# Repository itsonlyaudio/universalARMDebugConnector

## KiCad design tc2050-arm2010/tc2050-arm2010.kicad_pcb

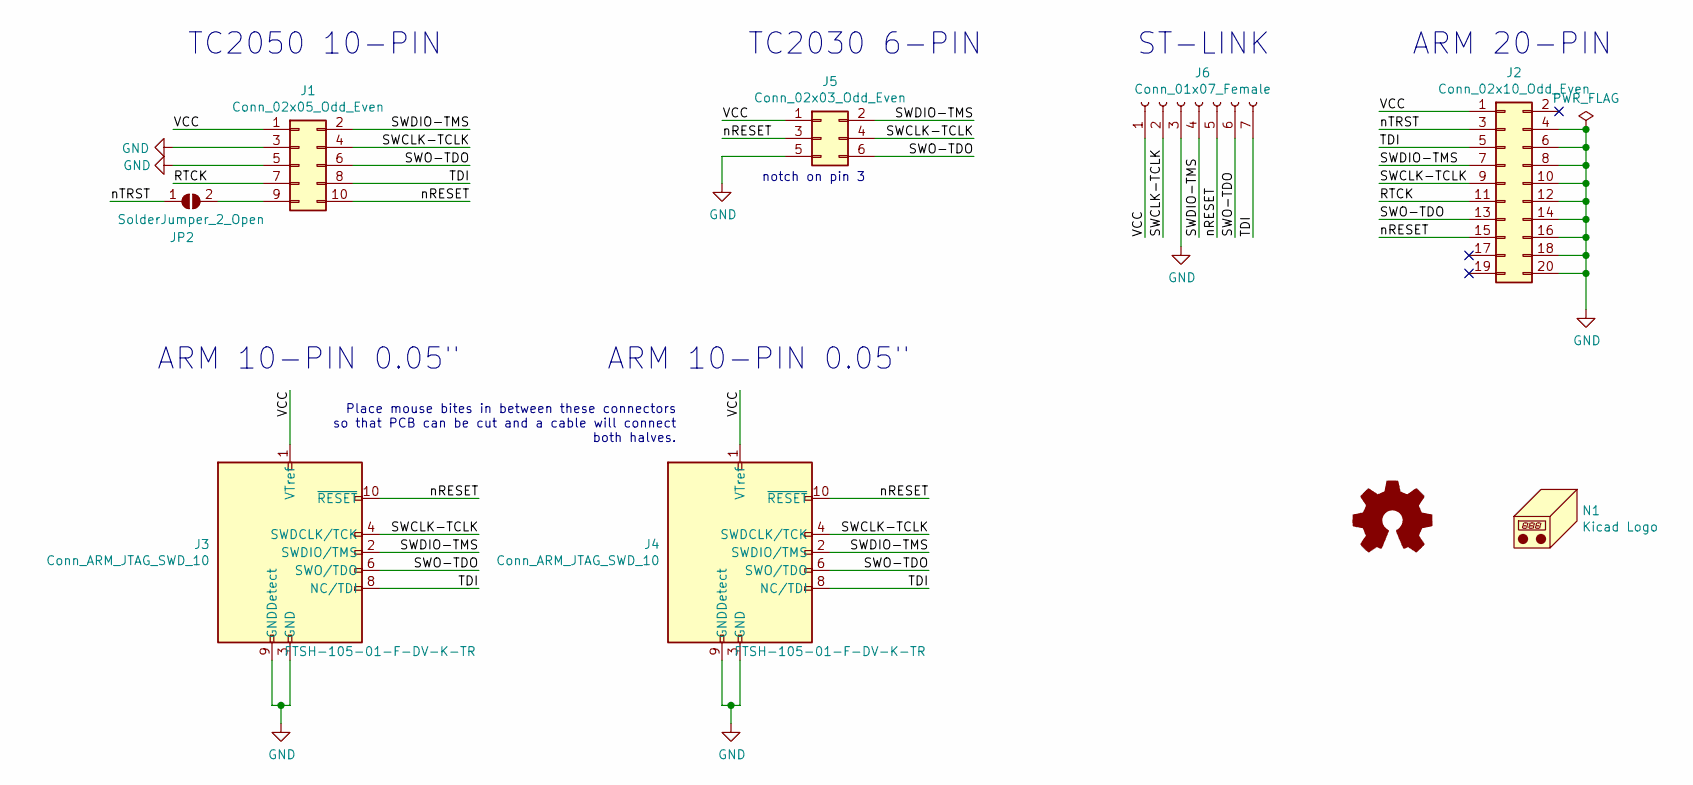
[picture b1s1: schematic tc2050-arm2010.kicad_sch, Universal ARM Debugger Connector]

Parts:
J1: Conn_02x05_Odd_Even; IDC-Header_2x05_P2.54mm_Vertical
J2: Conn_02x10_Odd_Even; PinSocket_2x10_P2.54mm_Horizontal
J3: Conn_ARM_JTAG_SWD_10; Samtec_MECF-05-02-NP-L-DV_2x05_P1.27mm_Socket_Horizontal; Partno FTSH-105-01-F-DV-K-TR; Digikey SAM13160CT-ND
J4: Conn_ARM_JTAG_SWD_10; Samtec_MECF-05-02-NP-L-DV_2x05_P1.27mm_Socket_Horizontal; Partno FTSH-105-01-F-DV-K-TR; Digikey SAM89SAM13160CT-ND
J5: Conn_02x03_Odd_Even; IDC-Header_2x03_P2.54mm_Vertical
J6: Conn_01x07_Female; PinHeader_1x07_P2.54mm_Vertical
JP2: SolderJumper_2_Open; SolderJumper-2_P1.3mm_Open_RoundedPad1.0x1.5mm
LOGO1: Logo_Open_Hardware_Small; OSHW-Logo2_7.3x6mm_SilkScreen
N1: Kicad Logo; KiCad-Logo2_5mm_SilkScreen

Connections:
/RTCK: J1.7, J2.11
/SWCLK-TCLK: J1.4, J2.9, J3.4 (SWDCLK/TCK), J4.4 (SWDCLK/TCK), J5.4, J6.2
/SWDIO-TMS: J1.2, J2.7, J3.2 (SWDIO/TMS), J4.2 (SWDIO/TMS), J5.2, J6.4
/SWO-TDO: J1.6, J2.13, J3.6 (SWO/TDO), J4.6 (SWO/TDO), J5.6, J6.6
/TDI: J1.8, J2.5, J3.8 (NC/TDI), J4.8 (NC/TDI), J6.7
/VCC: J1.1, J2.1, J3.1 (VTref), J4.1 (VTref), J5.1, J6.1
/nRESET: J1.10, J2.15, J3.10 (~RESET~), J4.10 (~RESET~), J5.3, J6.5
/nTRST: J2.3, JP2.1 (A)
GND: J1.3, J1.5, J2.4, J2.6, J2.8, J2.10, J2.12, J2.14, J2.16, J2.18, J2.20, J3.3 (GND), J3.5 (GND), J3.9 (GNDDetect), J4.3 (GND), J4.5 (GND), J4.9 (GNDDetect), J5.5, J6.3
unnamed: J1.9, JP2.2 (B)

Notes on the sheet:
TC2050 10-PIN
ARM 10-PIN 0.05"
Place mouse bites in between these connectors so that PCB can be cut and a cable will connect both halves.
notch on pin 3
TC2030 6-PIN
ST-LINK
ARM 20-PIN

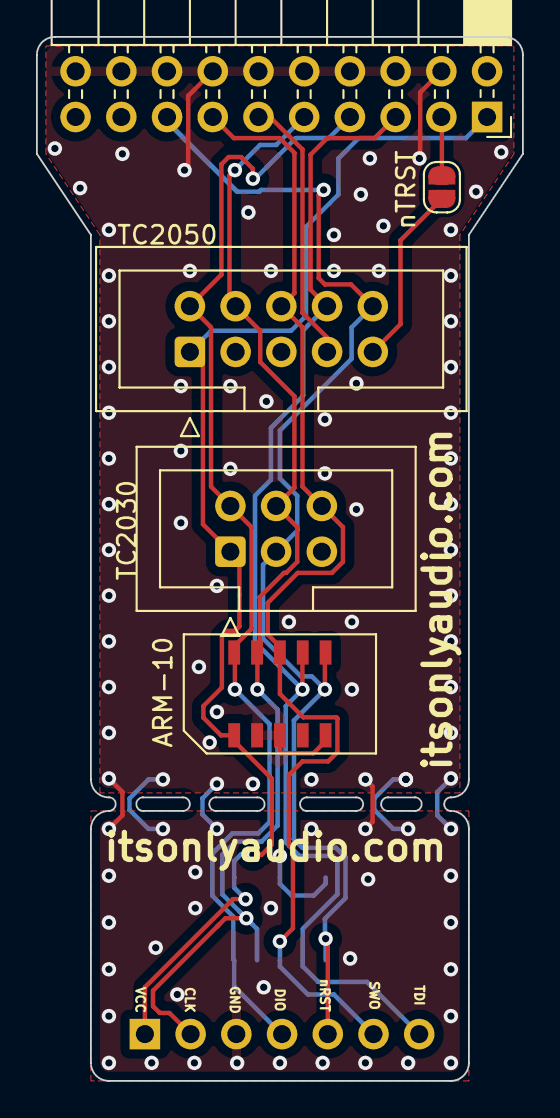
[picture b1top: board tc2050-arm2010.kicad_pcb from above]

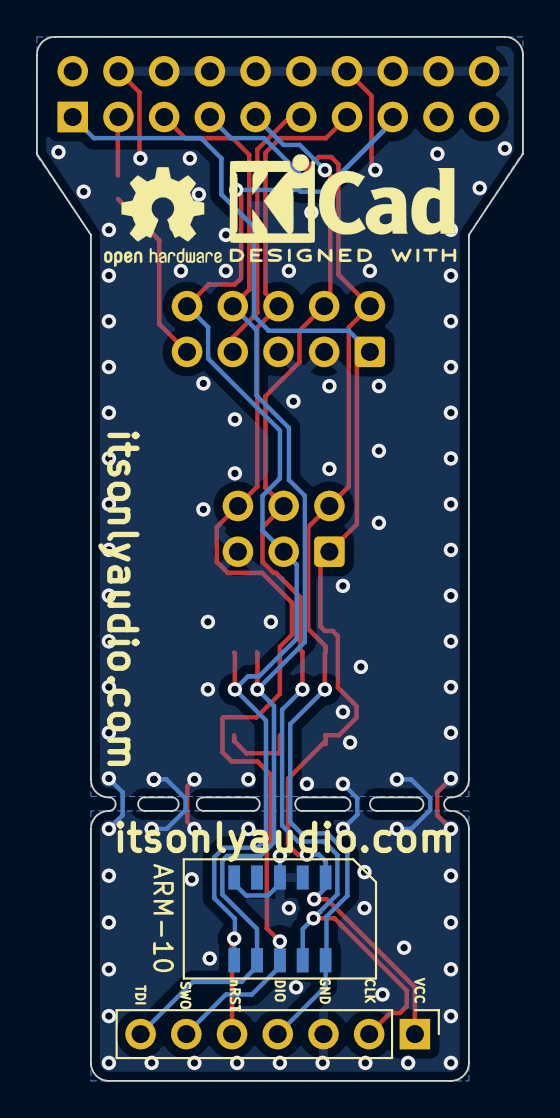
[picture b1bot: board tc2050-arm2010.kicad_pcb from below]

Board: 2 copper layers, 27.0 x 58.0 mm, 9 parts (4 on the bottom side), 10 nets.

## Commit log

2022-02-17 inital commit
2022-02-17 Trap for young players: gnd disconnected on host ARM10 when STM32 part cut off
2022-02-17 Latest exports for fabrication at JLCPCB and PCBWAY
2022-02-17 New version also has TC2030 header as well as ARM10 and breakaway board from ARM10 to 7-pin SWD
2022-02-17 deleting old backups
